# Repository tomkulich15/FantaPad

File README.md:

# 🍊 FantaPad
my surname is Fanta so i started thinking about the name of the name for the pad and for some reason I chose FantaPad i think its kinda funny 

now let get to the Features of the FantaPad
#Features
it have 6x buttons 1x rotary encoder with push button 
The 6x bottons are for shortcuts like copy,paste,cut,delet and so on
The rotary encoder is for volume and if you press it, it change layer
Layer 1: volume
layer 2: Zoom
layer 3: Scrub mode
The pad feature a RGB lighting

PCB Design:
The PCB was designed in KiCad

Here is the Schematic Picture for the Pad

I will also put images of the 3D print files here:
Here is the down part:

Here is the top part:

Here is in real life photo:

FantaPad Completed image:

Tutorial how to download the python to the board
1. Install CircuitPython:
   Hold the `BOOT` button on the XIAO RP2040, plug it into your PC, and copy the `.uf2` file to the `RPI-RP2` drive.

2. Install KMK:
   Download the KMK Firmware (https://github.com/KMKfw/kmk_firmware) and copy the `kmk` folder to the `lib` folder on your `CIRCUITPY` drive.

3. Upload Code:
   Copy the provided `code.py` to the root of the `CIRCUITPY` drive.

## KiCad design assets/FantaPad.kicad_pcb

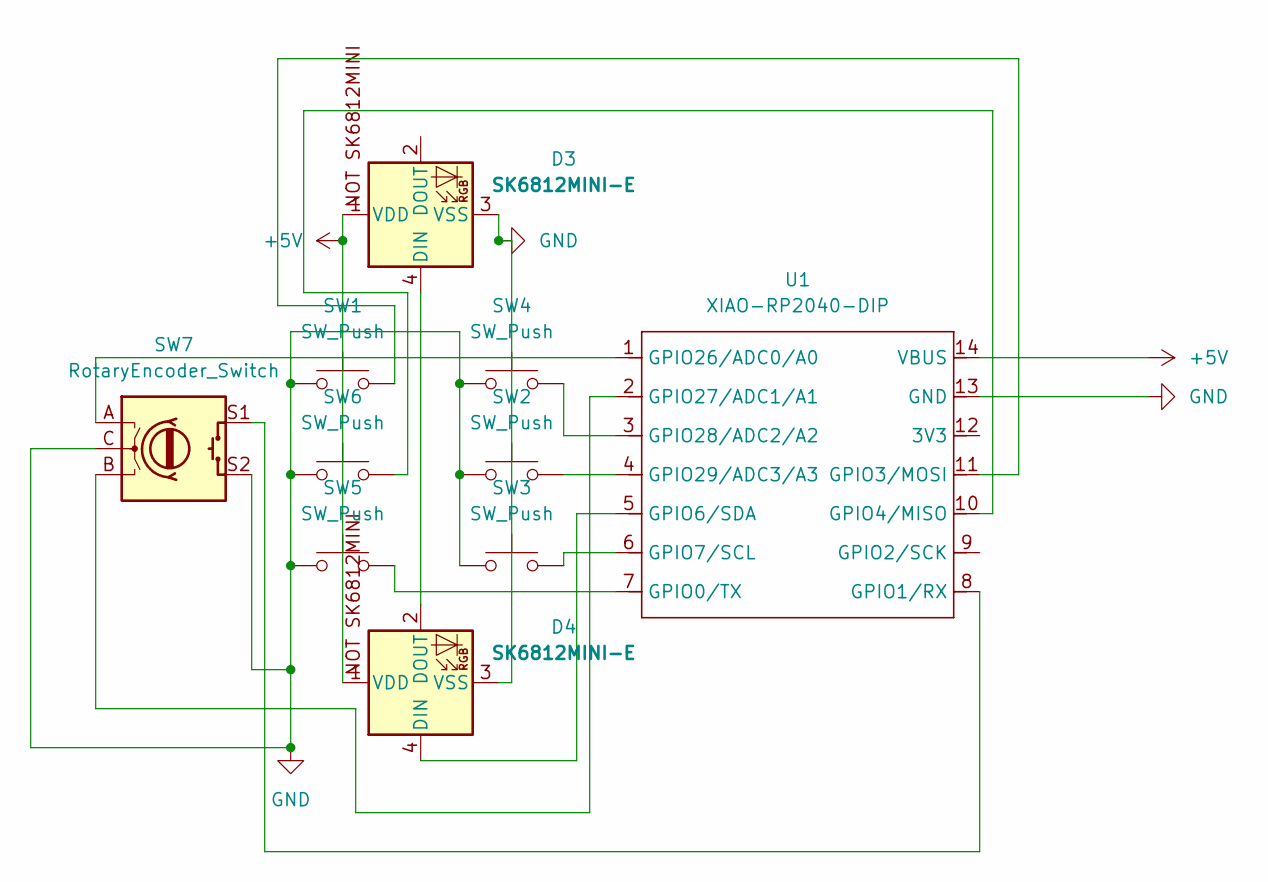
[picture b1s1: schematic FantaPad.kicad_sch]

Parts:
D3, D4: SK6812MINI-E; SK6812MINI-E_fixed
SW1, SW2, SW3, SW4, SW5, SW6: SW_Push; SW_Cherry_MX_1.00u_PCB
SW7: RotaryEncoder_Switch; RotaryEncoder_Alps_EC11E-Switch_Vertical_H20mm
U1: XIAO-RP2040-DIP

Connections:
+5V: D3.1 (VDD), D4.1 (VDD), U1.14 (VBUS)
GND: D3.3 (VSS), D4.3 (VSS), SW1.1, SW2.1, SW3.1, SW4.1, SW5.1, SW6.1, SW7.C, SW7.S2, U1.13 (GND)
unnamed: D3.4 (DIN), D4.2 (DOUT)
unnamed: D4.4 (DIN), U1.5 (GPIO6/SDA)
unnamed: SW5.2, U1.7 (GPIO0/TX)
unnamed: SW7.S1, U1.8 (GPIO1/RX)
unnamed: SW1.2, U1.11 (GPIO3/MOSI)
unnamed: SW6.2, U1.10 (GPIO4/MISO)
unnamed: SW3.2, U1.6 (GPIO7/SCL)
unnamed: SW7.A, U1.1 (GPIO26/ADC0/A0)
unnamed: SW7.B, U1.2 (GPIO27/ADC1/A1)
unnamed: SW4.2, U1.3 (GPIO28/ADC2/A2)
unnamed: SW2.2, U1.4 (GPIO29/ADC3/A3)

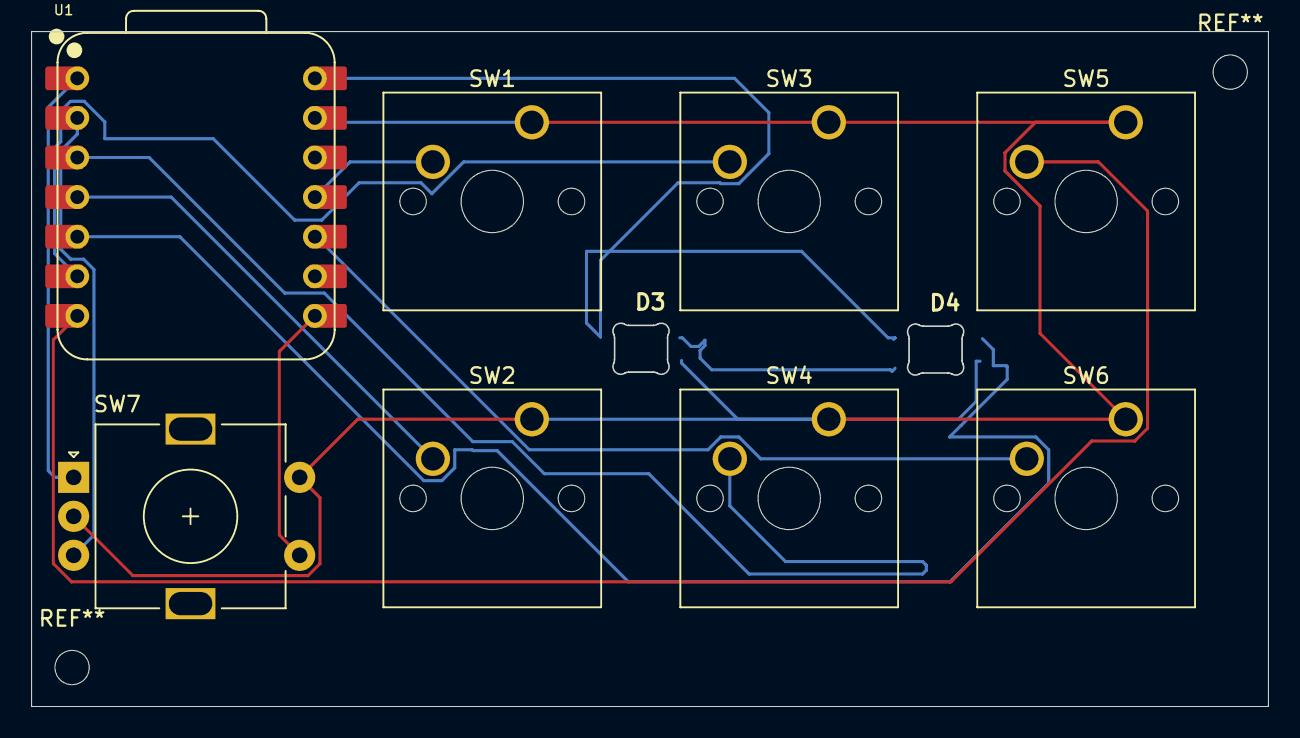
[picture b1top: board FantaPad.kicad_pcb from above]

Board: 2 copper layers, 79.3 x 43.2 mm, 10 parts (0 on the bottom side), 13 nets.

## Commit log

2025-12-03 Initialize keyboard with media keys and layers
2025-12-03 Revise README.md with project details and instructions
    Updated README.md to include detailed project information, features, hardware specifications, and setup instructions for the FantaPad macropad.
2025-12-04 Create assets
2025-12-04 Update PCB design image in README
2025-12-04 Fix image path for PCB design in README
2025-12-04 Add schematic image to README
2025-12-04 Update README with installation tutorial
    Added tutorial instructions for installing CircuitPython and KMK.
2025-12-04 Add images of 3D print files to README
2025-12-04 Modify comment format for 3D print files section
    Updated README to change comment format for 3D print files section.
2025-12-04 Revise installation tutorial in README.md
    Updated tutorial steps for installing CircuitPython and KMK.
2025-12-11 Create pes
2025-12-11 Rename FantaPad Down.stl to Stlfiles/FantaPad Down.stl
2025-12-11 Update README with completed image and tutorial
    Added completed image and tutorial for CircuitPython installation.
2025-12-11 Rename FantaPadDown.stl to FantaPadDown.stl
2025-12-11 Rename FantaPadTop.png to FantaPadTop.png
2025-12-11 Rename FantaPadDown.png to FantaPadDown.png
2025-12-11 Rename FantaPadTop.stl to FantaPadTop.stl
2025-12-11 Rename Code.py to Code.py
2025-12-11 Rename FantaPadComplete.png to FantaPadComplete.png
2025-12-11 Rename FantaPadPCB.png to FantaPadPCB.png
2025-12-11 Rename FantaPadSchematic.png to FantaPadSchematic.png
2026-06-06 Update image reference in README
2026-06-06 Change image format from PNG to JPEG in README
